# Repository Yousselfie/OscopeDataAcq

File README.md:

# Oscilloscope Data Acquisition
Programs related to the gathering of EM (electromagnetic) wave data from the processing unit of a PLC (programmable logic controller) as it runs various control logic.

## Use of Arduino
In order to capture the EM data of a specific control logic, it must be running on the controller. Normally, this would mean connecting the PLC to the PC, downloading the control logic to the PLC, then running it. This becomes a tedious process when there are many possible symbolic paths of specific control logic for the PLC to run and for data to be collected from. To make this process more efficient, we make use of a microcontroller (Arduino) to automatically modify the inputs of a PLC to simulate new control logic. Given all the symbolic execution paths in a control logic, the Arduino will set and unset inputs on the PLC to match each one for a set amount of time before the next path is simulated. This allows for continous data collection using the oscilloscope.  
## Project Directories
**./ControlPLC** - Contains code relating to writing/reading to the Arduino controlling the PLC inputs and accessing the PLC outputs.  
**./ControlPLC/src** - Contains the source code and pseudocode for the main cpp file uploaded into the microcontroller. This code defines how the Arduino communicates with and interprets data from the local machine (Python controller).  
**./ControlPLC/python_controllers** - Contains multiple different Python programs that each establish communication with the Arduino, send data to be parsed, and ultimately determine PLC I/O from the Arduino. Each of these has been used for a different testing purpose (such as turning on all the PLC inputs or running through all symbolic paths of a sample program and turning on/off inputs based on each path).  

**./SignalProcessing** - Contains scripts for cleaning and comparing captured signals in CSV format. Most important is the script that compares two signals using dynamic time warping and the script that compares two signals after wavelet denoising them.

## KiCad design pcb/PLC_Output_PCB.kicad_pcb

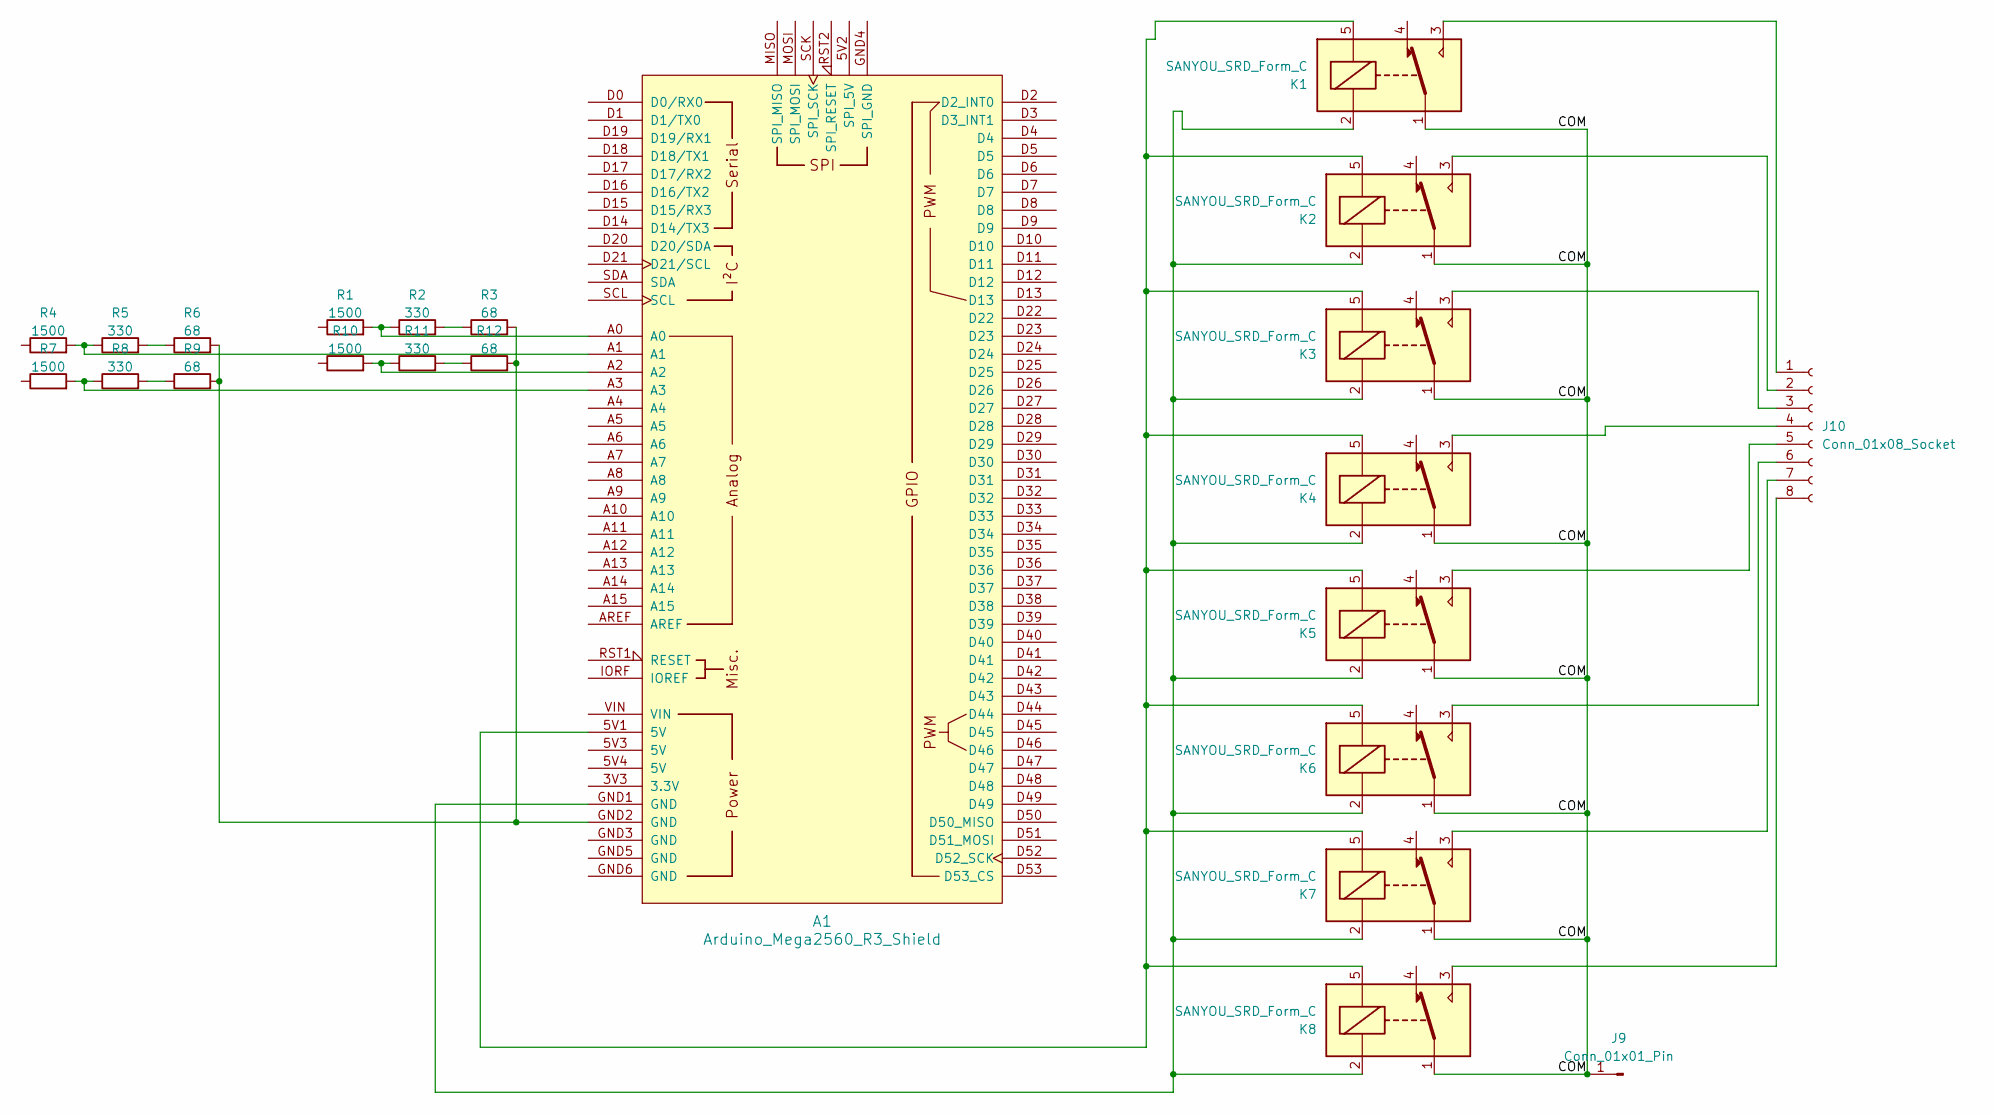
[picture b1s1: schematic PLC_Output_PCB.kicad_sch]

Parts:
A1: Arduino_Mega2560_R3_Shield
J9: Conn_01x01_Pin; PinHeader_1x01_P1.00mm_Vertical
J10: Conn_01x08_Socket; PinSocket_1x08_P1.00mm_Vertical
K1, K2, K3, K4, K5, K6, K7, K8: SANYOU_SRD_Form_C; Relay_SPDT_SANYOU_SRD_Series_Form_C
R1, R4, R7, R10: 1500; R_Axial_DIN0207_L6.3mm_D2.5mm_P7.62mm_Horizontal_CUSTOM
R2, R5, R8, R11: 330; R_Axial_DIN0207_L6.3mm_D2.5mm_P7.62mm_Horizontal_CUSTOM
R3, R6, R9, R12: 68; R_Axial_DIN0207_L6.3mm_D2.5mm_P7.62mm_Horizontal_CUSTOM

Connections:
/COM: J9.1, K1.1, K2.1, K3.1, K4.1, K5.1, K6.1, K7.1, K8.1
unnamed: A1.5V1 (5V), K1.5, K2.5, K3.5, K4.5, K5.5, K6.5, K7.5, K8.5
unnamed: A1.GND1 (GND), K1.2, K2.2, K3.2, K4.2, K5.2, K6.2, K7.2, K8.2
unnamed: A1.GND2 (GND), R3.2, R6.2, R9.2, R12.2
unnamed: A1.A0, R1.2, R2.1
unnamed: A1.A1, R4.2, R5.1
unnamed: A1.A2, R10.2, R11.1
unnamed: A1.A3, R7.2, R8.1
unnamed: J10.1, K1.3
unnamed: J10.2, K2.3
unnamed: J10.3, K3.3
unnamed: J10.4, K4.3
unnamed: J10.5, K5.3
unnamed: J10.6, K6.3
unnamed: J10.7, K7.3
unnamed: J10.8, K8.3
unnamed: R2.2, R3.1
unnamed: R5.2, R6.1
unnamed: R8.2, R9.1
unnamed: R11.2, R12.1

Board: 2 copper layers, 23 parts (0 on the bottom side), 20 nets, no tracks yet.

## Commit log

2025-05-21 Established serial communication between Arduino and PC + programmed the changing of inputs based on python outputs
2025-05-21 Updated Arduino code to allow for dynamic amount of inputs and outputs to/from the PLC. Maximum of 27 inputs and 27 outputs.
2025-05-21 Added missing pinMode calls and switched usage of LOW and HIGH to account for relay being normally closed (NC relay).
2025-05-22 Added to readme
2025-05-22 Code cleaning
2025-05-27 Created folder for python files
2025-05-27 Added project directory information to readme
2025-05-27 Updated gitignore to ignore README edit files
2025-06-18 Signal processing code
2025-06-18 CSV files for testing impact of PLC input combinations on EM radiation
2025-06-23 Input comparison script for EM captures
2025-06-23 DTW code
2025-06-25 Program to read voltage from analog input
2025-06-25 Reading 4 arduino analog inputs for voltage
2025-06-26 Cleanup with helper functions
2025-06-30 Cleaned up code with functions; Added output reading and checking if it matches expected output
2025-06-30 Output checking
2025-07-01 Start of pcb schematic creation
2025-07-02 Started PCB
2025-07-03 Added analog testing arduino code and analog testing control logic
2025-07-03 Added helpful comments to the top of main.cpp in ControlPLC/src
2025-07-21 Updated code
2025-07-30 Req.txt and .gitignore
2025-08-01 Added single_graphy.py script
2025-08-01 Added controller.py
2025-08-11 Update files
2025-08-11 Evaluation
2025-08-12 Input-to-start traffic logic
2025-08-12 uncommented input-to-start
